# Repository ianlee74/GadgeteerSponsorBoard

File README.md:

GadgeteerSponsorBoard
=====================

A Gadgeteer mounting board with a built-in LED array that acts as a Gadgeteer module and is used to highlight a sponsor's logo.

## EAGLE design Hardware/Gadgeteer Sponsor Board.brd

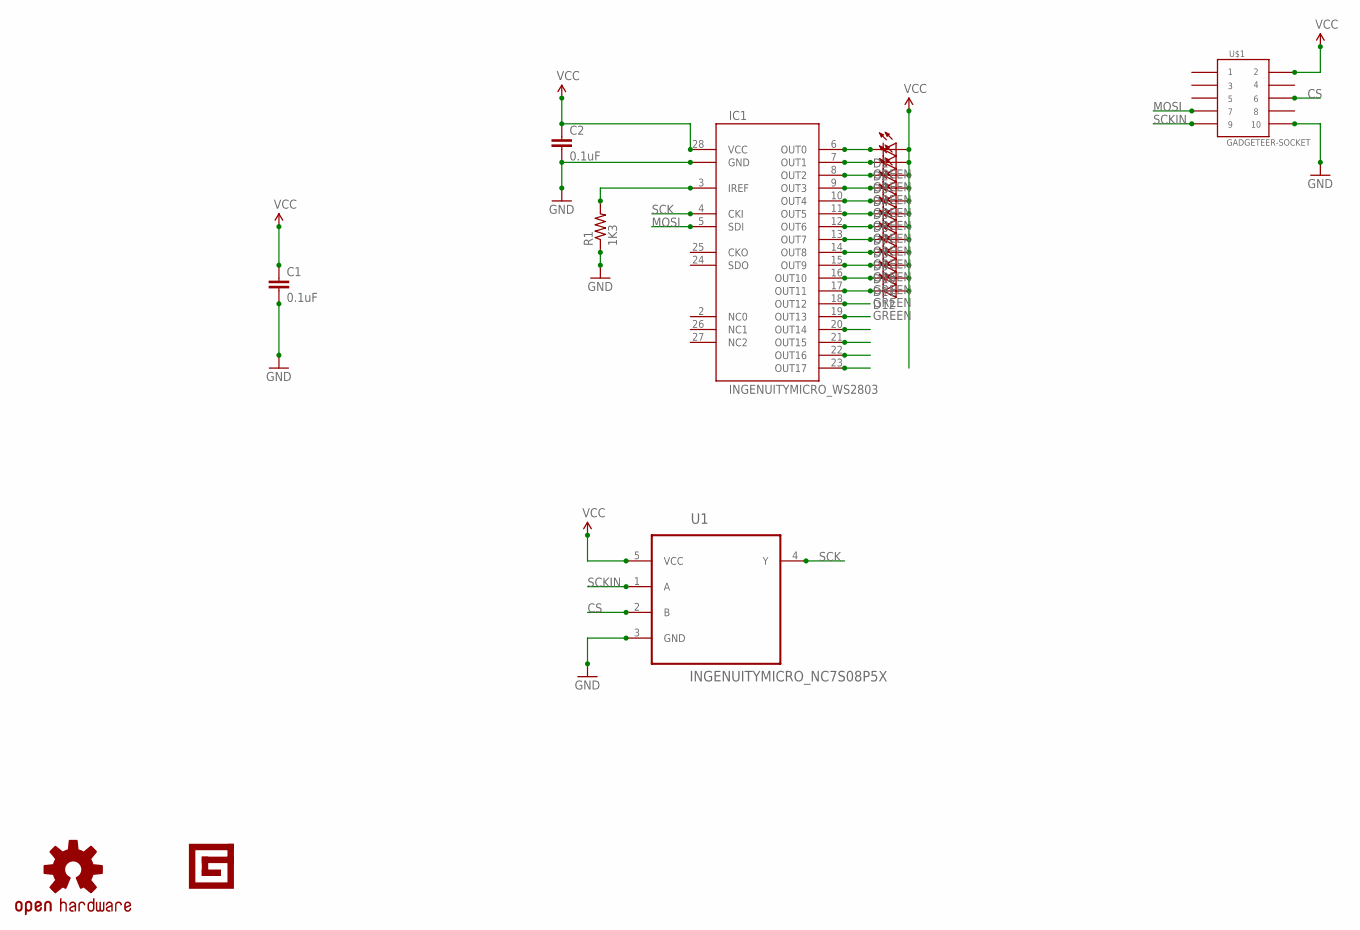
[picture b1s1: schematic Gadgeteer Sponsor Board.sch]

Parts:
C1, C2: 0.1uF; SPARKFUN_0603-CAP
D1, D2, D3, D4, D5, D6, D7, D8, D9, D10, D11, D12: GREEN; LED-0603
IC1: INGENUITYMICRO_WS2803; INGENUITYMICRO_SO28W
LOGO1: OSHW-LOGOL; OSHW-LOGO-L
R1: 1K3; RESISTOR_R0603
U1: INGENUITYMICRO_NC7S08P5X; INGENUITYMICRO_SOT65P210X110-5N
U$1: GADGETEER-SOCKET; 2X5_1.27MM
U$2: INGENUITYMICRO_LOGO_LOGO-GADGETEER-NORMAL; INGENUITYMICRO_LOGO_GADGETEER-SILK

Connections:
CS: U1.2 (B), U$1.6
GND: C1.2, C2.2, IC1.1 (GND), R1.1, U1.3 (GND), U$1.10
MOSI: IC1.5 (SDI), U$1.7
unnamed: D1.C, IC1.6 (OUT0)
unnamed: D2.C, IC1.7 (OUT1)
unnamed: IC1.3 (IREF), R1.2
unnamed: D3.C, IC1.8 (OUT2)
unnamed: D4.C, IC1.9 (OUT3)
unnamed: D5.C, IC1.10 (OUT4)
unnamed: D6.C, IC1.11 (OUT5)
unnamed: D7.C, IC1.12 (OUT6)
unnamed: D8.C, IC1.13 (OUT7)
unnamed: D9.C, IC1.14 (OUT8)
unnamed: D10.C, IC1.15 (OUT9)
unnamed: D11.C, IC1.16 (OUT10)
unnamed: D12.C, IC1.17 (OUT11)
SCK: IC1.4 (CKI), U1.4 (Y)
SCKIN: U1.1 (A), U$1.9
VCC: C1.1, C2.1, D1.A, D2.A, D3.A, D4.A, D5.A, D6.A, D7.A, D8.A, D9.A, D10.A, D11.A, D12.A, IC1.28 (VCC), U1.5 (VCC), U$1.2

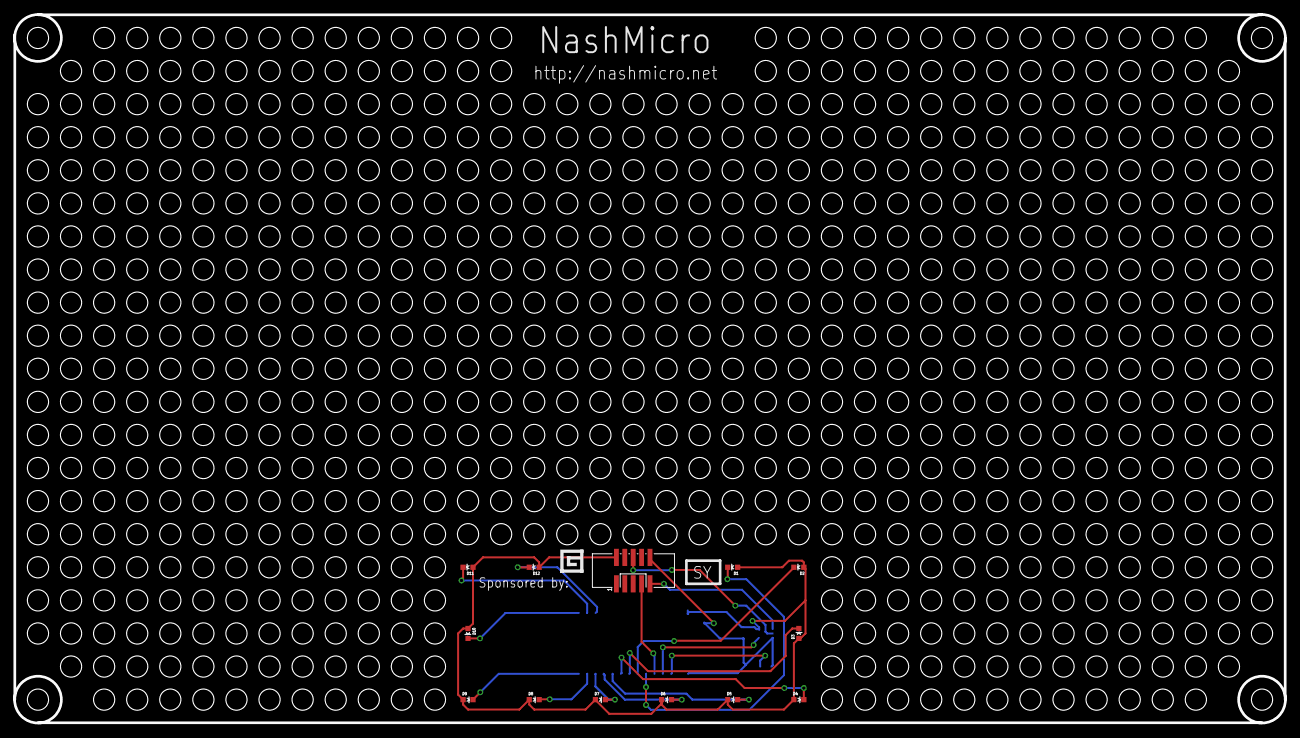
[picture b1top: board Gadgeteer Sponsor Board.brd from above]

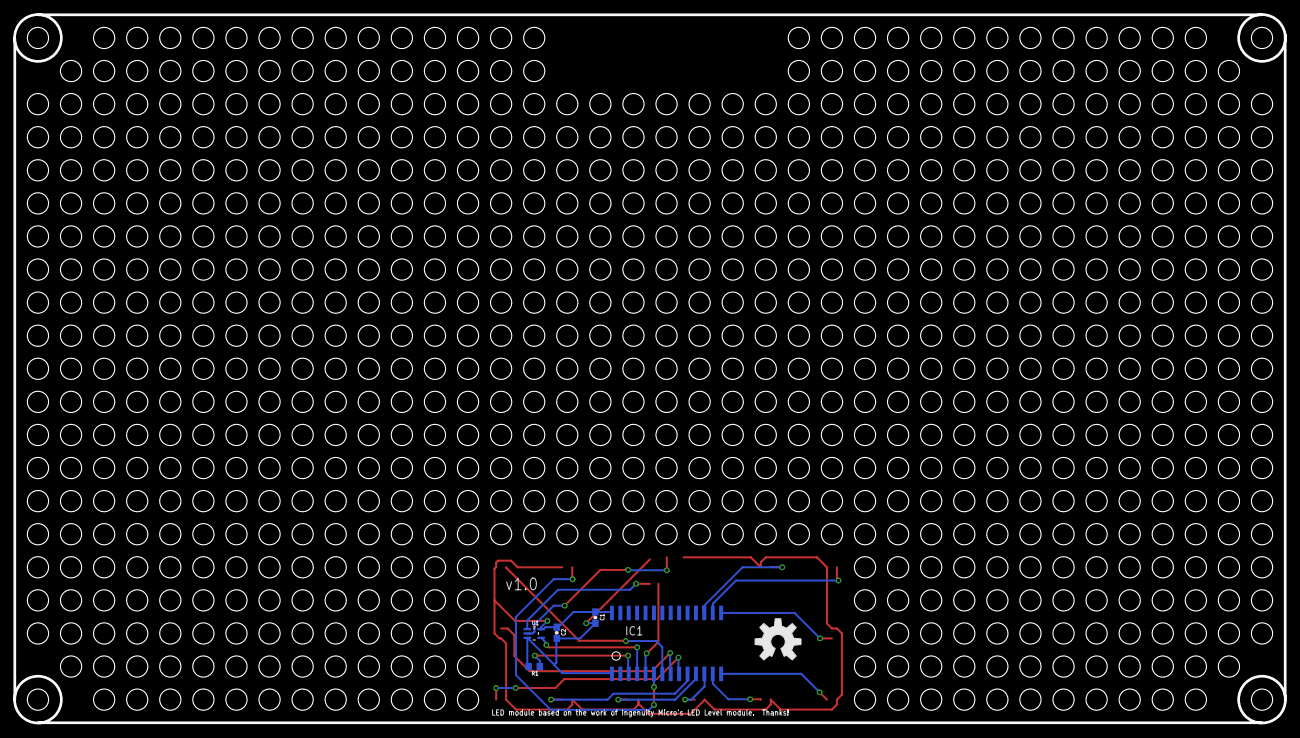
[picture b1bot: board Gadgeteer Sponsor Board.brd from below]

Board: 2 copper layers, 192.1 x 107.1 mm, 20 parts (6 on the bottom side), 19 nets.

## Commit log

2013-07-26 Initial add of v1.0 design as was submitted to DFRobot.
2013-07-26 Fixed socket label. Made it 'SY' instead of 'X'.
2013-08-18 Added Pong demo project.
2014-09-09 Updated to work with GHI SDK v4.6.2.
2015-02-21 Upgraded demo project to latest 4.2 frameworks. Compiles but not tested with hardware.

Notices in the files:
parts and their libraries:
SparkFun-LED: Licensing: CC v3.0 Share-Alike You are welcome to use this library for commercial purposes.
